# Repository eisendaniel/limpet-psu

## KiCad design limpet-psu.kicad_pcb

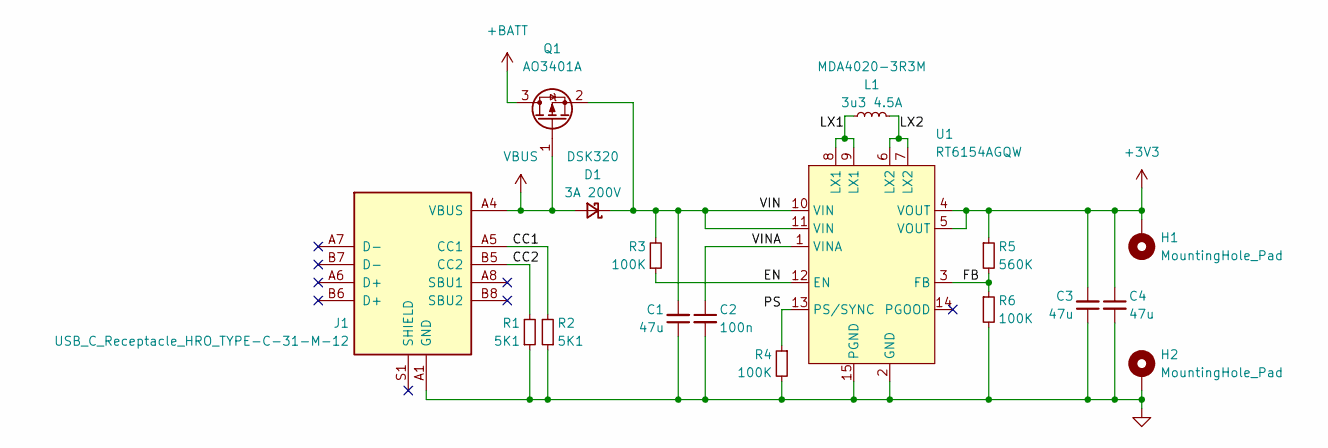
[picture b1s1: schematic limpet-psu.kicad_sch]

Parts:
C1, C3, C4: 47u; C_0805_2012Metric
C2: 100n; C_0201_0603Metric
D1: 3A 200V; D_SOD-123F; Mfr. Part # DSK320
H1, H2: MountingHole_Pad; MountingHole_2.2mm_M2_Pad_Via
J1: USB_C_Receptacle_HRO_TYPE-C-31-M-12
L1: 3u3 4.5A; L_Taiyo-Yuden_NR-50xx; Mfr. Part # MDA4020-3R3M
Q1: AO3401A; SOT-23
R1, R2: 5K1; R_0201_0603Metric
R3, R4, R6: 100K; R_0201_0603Metric
R5: 560K; R_0201_0603Metric
U1: RT6154AGQW; DFN-14-1EP_3x4mm_P0.5mm_EP1.7x3.3mm

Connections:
+3V3: C3.2, C4.1, H1.1, R5.1, U1.4 (VOUT), U1.5 (VOUT)
+BATT: Q1.3 (D)
/CC1: J1.A5 (CC1), R2.2
/CC2: J1.B5 (CC2), R1.2
/EN: R3.1, U1.12 (EN)
/FB: R5.2, R6.1, U1.3 (FB)
/LX1: L1.1, U1.8 (LX1), U1.9 (LX1)
/LX2: L1.2, U1.6 (LX2), U1.7 (LX2)
/PS: R4.1, U1.13 (PS/SYNC)
/VIN: C1.2, D1.1 (K), Q1.2 (S), R3.2, U1.10 (VIN), U1.11 (VIN)
/VINA: C2.1, U1.1 (VINA)
GND: C1.1, C2.2, C3.1, C4.2, H2.1, J1.A1 (GND), J1.A12 (GND), J1.B1 (GND), J1.B12 (GND), R1.1, R2.1, R4.2, R6.2, U1.2 (GND), U1.15 (PGND)
VBUS: D1.2 (A), J1.A4 (VBUS), J1.A9 (VBUS), J1.B4 (VBUS), J1.B9 (VBUS), Q1.1 (G)

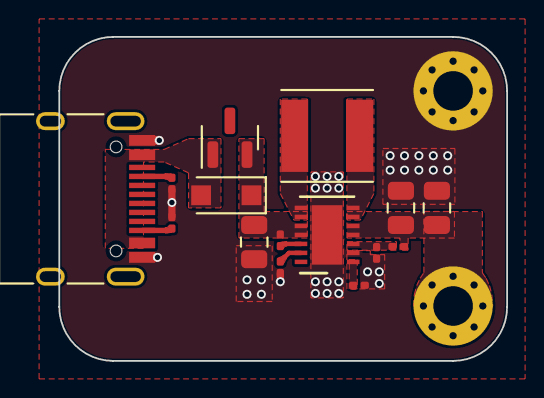
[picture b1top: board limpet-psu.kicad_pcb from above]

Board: 2 copper layers, 24.9 x 18.0 mm, 17 parts (0 on the bottom side), 12 nets.

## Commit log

2022-08-25 init
2022-08-25 output
2022-08-25 zones cleaned
2022-08-26 2ndary
